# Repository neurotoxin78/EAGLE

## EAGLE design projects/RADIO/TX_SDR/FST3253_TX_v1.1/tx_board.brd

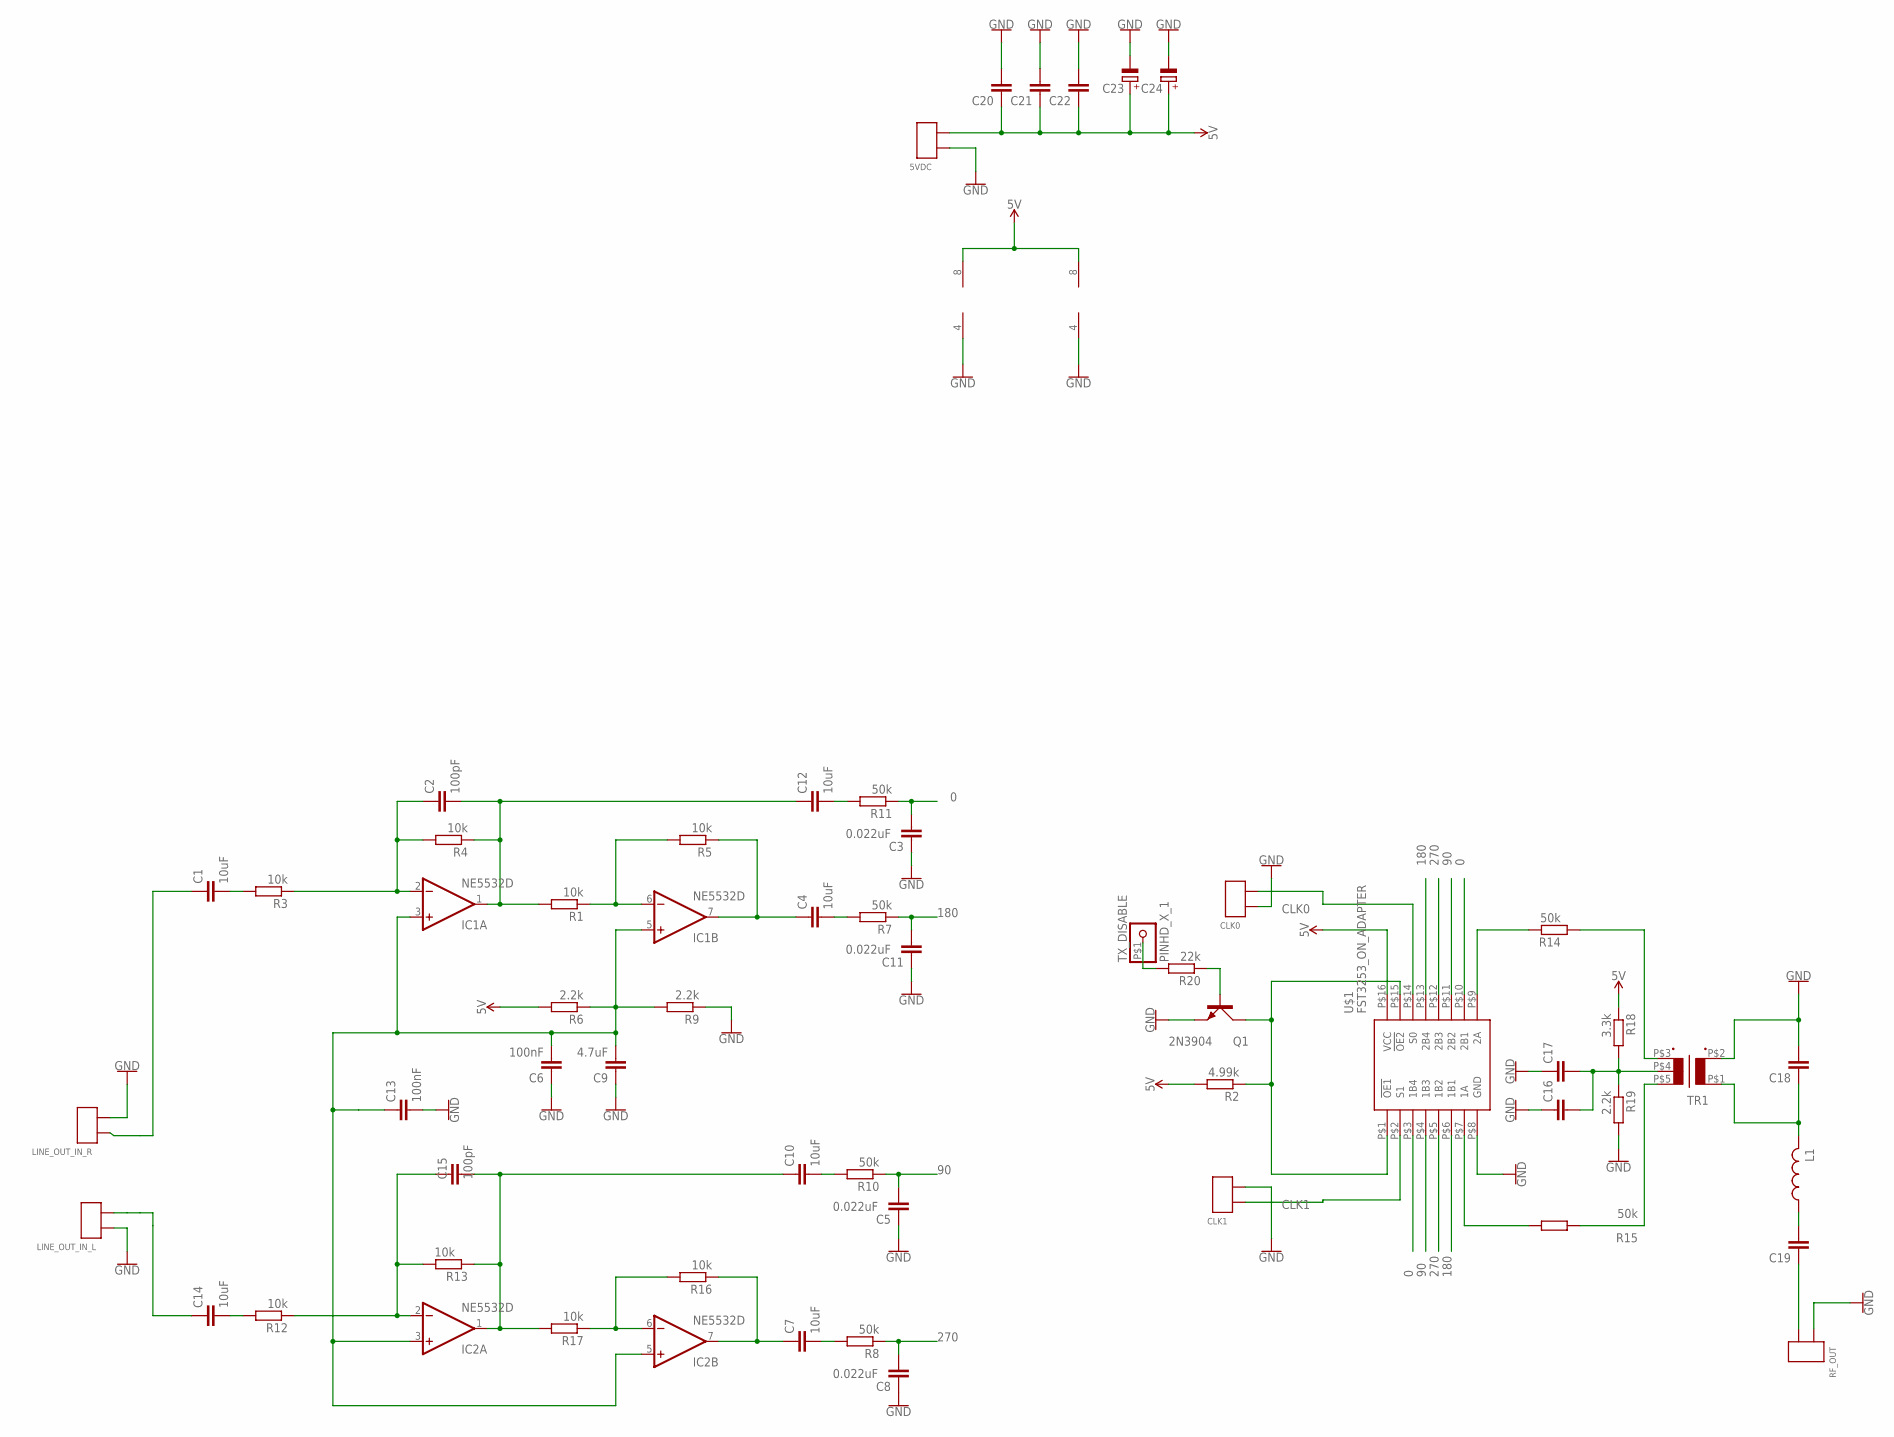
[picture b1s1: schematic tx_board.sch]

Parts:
5VDC: 2X_SMD_PTH_PIN; 2X_SMD_PTH
C1, C4, C7, C10, C12, C14: 10uF; C0805K
C2, C15: 100pF; C0805K
C3, C5, C8, C11: 0.022uF; C0805
C6, C13: 100nF; C0805
C9: 4.7uF; C0805
C16, C20, C21, C22: C_0805_SMD; C0805
C17, C18, C19: C_0805_PTH; C0805K
C23, C24: C_POL; E5-5
CLK0, CLK1: 2X_SMD_PTH_PIN; 2X_SMD_PTH
IC1, IC2: NE5532D; SO08
L1: L_0805_PTH; M0805
LINE_OUT_IN_L: 2X_SMD_PTH_PIN; 2X_SMD_PTH
LINE_OUT_IN_R: 2X_SMD_PTH_PIN; 2X_SMD_PTH
Q1: 2N3904; TO92D
R1, R3, R4, R12, R13, R16: 10k; R0805
R2: 4.99k; R0805W
R5, R17: 10k; R0805W
R6: 2.2k; 0204/7
R7, R8, R10, R11, R14, R15: 50k; R0805
R9, R19: 2.2k; R0805W
R18: 3.3k; R0805W
R20: 22k; R0805W
RF_OUT: 2X_SMD_PTH_PIN; 2X_SMD_PTH
TR1: 5PIN_TRANSFORMER
TX_DISABLE: PINHD_X_1; PINHD1
U$1: FST3253_ON_ADAPTER; SSOP16_ADAPTER

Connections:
0: C3.2, R11.1, R11.P$1 (1), U$1.P$3 (1B4), U$1.P$10 (2B1)
5V: 5VDC.P$2 (PIN1), 5VDC.T$2 (PIN1), C20.1, C21.1, C22.1, C23.+, C24.+, IC1.8 (V+), IC2.8 (V+), R2.2, R6.2, R18.1, U$1.P$16 (VCC)
90: C5.2, R10.1, R10.P$1 (1), U$1.P$4 (1B3), U$1.P$11 (2B2)
180: C11.2, R7.1, R7.P$1 (1), U$1.P$6 (1B1), U$1.P$13 (2B4)
270: C8.2, R8.1, R8.P$1 (1), U$1.P$5 (1B2), U$1.P$12 (2B3)
CLK0: CLK0.P$2 (PIN1), CLK0.T$2 (PIN1), U$1.P$14 (S0)
CLK1: CLK1.P$1 (PIN0), CLK1.T$1 (PIN0), U$1.P$2 (S1)
GND: 5VDC.P$1 (PIN0), 5VDC.T$1 (PIN0), C3.1, C5.1, C6.1, C8.1, C9.1, C11.1, C13.2, C16.1, C17.1, C17.P$1 (1), C18.2, C18.P$2 (2), C20.2, C21.2, C22.2, C23.-, C24.-, CLK0.P$1 (PIN0), CLK0.T$1 (PIN0), CLK1.P$2 (PIN1), CLK1.T$2 (PIN1), IC1.4 (V-), IC2.4 (V-), LINE_OUT_IN_L.P$1 (PIN0), LINE_OUT_IN_L.T$1 (PIN0), LINE_OUT_IN_R.P$2 (PIN1), LINE_OUT_IN_R.T$2 (PIN1), Q1.E, R9.1, R19.2, RF_OUT.P$1 (PIN0), RF_OUT.T$1 (PIN0), TR1.P$2 (2), U$1.P$8 (GND)
unnamed: Q1.C, R2.1, U$1.P$1 (!OE1), U$1.P$15 (!OE2)
unnamed: R15.2, R15.P$2 (2), U$1.P$7 (1A)
unnamed: R14.2, R14.P$2 (2), U$1.P$9 (2A)
unnamed: R14.1, R14.P$1 (1), TR1.P$3 (3)
unnamed: R15.1, R15.P$1 (1), TR1.P$5 (5)
unnamed: C16.2, C17.2, C17.P$2 (2), R18.2, R19.1, TR1.P$4 (4)
unnamed: C2.1, C2.P$1 (1), IC1.2 (-IN), R3.1, R3.P$1 (1), R4.2, R4.P$2 (2)
unnamed: C18.1, C18.P$1 (1), L1.2, L1.P$2 (2), TR1.P$1 (1)
unnamed: C19.2, C19.P$2 (2), L1.1, L1.P$1 (1)
unnamed: C2.2, C2.P$2 (2), C12.1, C12.P$1 (1), IC1.1 (OUT), R1.2, R1.P$2 (2), R4.1, R4.P$1 (1)
unnamed: IC1.6 (-IN), R1.1, R1.P$1 (1), R5.2
unnamed: C15.1, C15.P$1 (1), IC2.2 (-IN), R12.1, R12.P$1 (1), R13.2, R13.P$2 (2)
unnamed: C10.1, C10.P$1 (1), C15.2, C15.P$2 (2), IC2.1 (OUT), R13.1, R13.P$1 (1), R17.2
unnamed: IC2.6 (-IN), R16.2, R16.P$2 (2), R17.1
unnamed: C4.1, C4.P$1 (1), IC1.7 (OUT), R5.1
unnamed: C7.1, C7.P$1 (1), IC2.7 (OUT), R16.1, R16.P$1 (1)
unnamed: C4.2, C4.P$2 (2), R7.2, R7.P$2 (2)
unnamed: C19.1, C19.P$1 (1), RF_OUT.P$2 (PIN1), RF_OUT.T$2 (PIN1)
unnamed: C1.1, C1.P$1 (1), LINE_OUT_IN_R.P$1 (PIN0), LINE_OUT_IN_R.T$1 (PIN0)
unnamed: C14.1, C14.P$1 (1), LINE_OUT_IN_L.P$2 (PIN1), LINE_OUT_IN_L.T$2 (PIN1)
unnamed: Q1.B, R20.1
unnamed: C14.2, C14.P$2 (2), R12.2, R12.P$2 (2)
unnamed: C1.2, C1.P$2 (2), R3.2, R3.P$2 (2)
unnamed: R20.2, TX_DISABLE.P$1
unnamed: C12.2, C12.P$2 (2), R11.2, R11.P$2 (2)
unnamed: C10.2, C10.P$2 (2), R10.2, R10.P$2 (2)
unnamed: C7.2, C7.P$2 (2), R8.2, R8.P$2 (2)
unnamed: C6.2, C9.2, C13.1, IC1.3 (+IN), IC1.5 (+IN), IC2.3 (+IN), IC2.5 (+IN), R6.1, R9.2

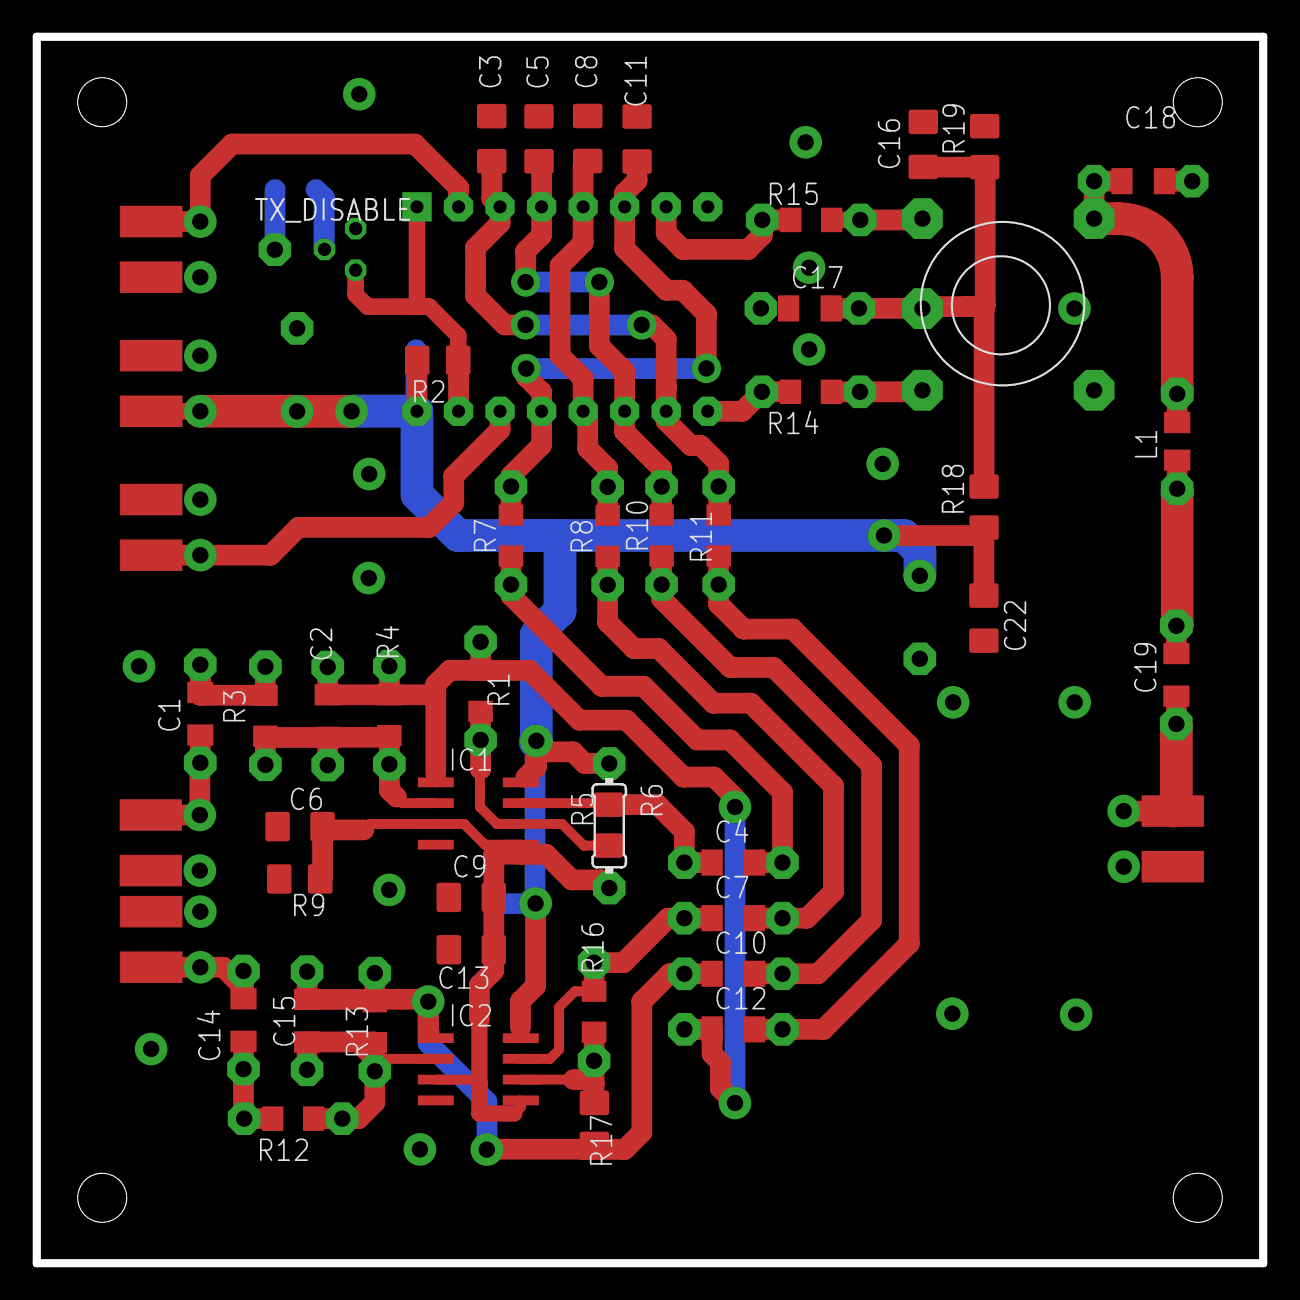
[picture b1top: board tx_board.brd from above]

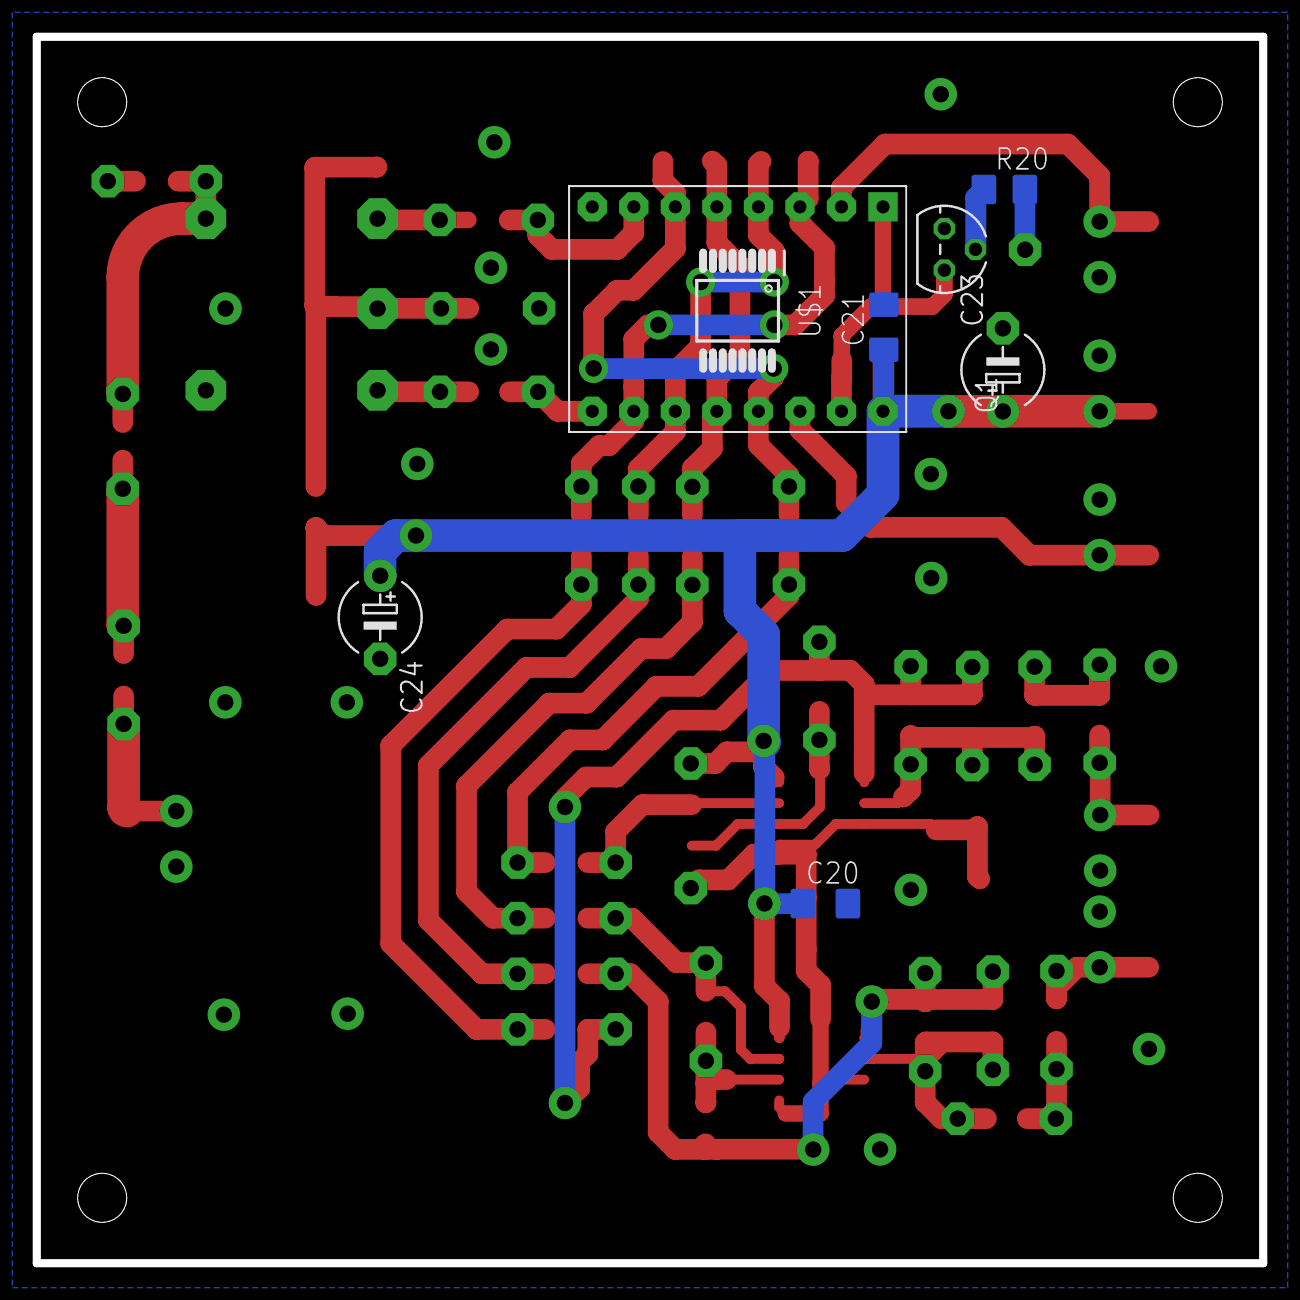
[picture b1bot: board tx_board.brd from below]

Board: 2 copper layers, 75.0 x 75.0 mm, 57 parts (7 on the bottom side), 36 nets.

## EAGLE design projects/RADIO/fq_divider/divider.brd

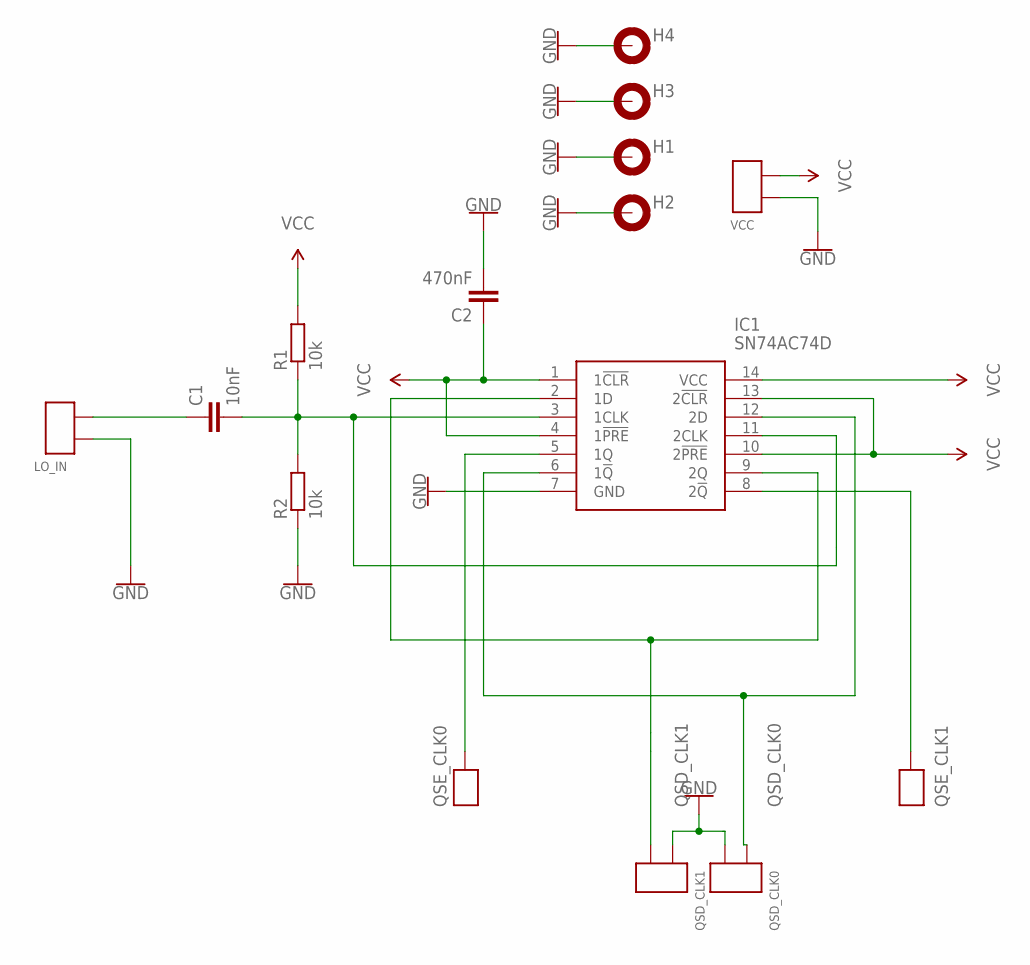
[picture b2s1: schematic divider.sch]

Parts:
C1: 10nF; C0805
C2: 470nF; C0805
H1, H2: MOUNT-PAD-ROUND3.0; 3,0-PAD
H3, H4: MOUNT-PAD-ROUND2.8; 2,8-PAD
IC1: SN74AC74D; SOIC127P600X175-14N
LO_IN: 2X_SMD_PTH_PIN; 2X_SMD_PTH
QSD_CLK0, QSD_CLK1: 2X_SMD_PTH_PIN; 2X_SMD_PTH
R1, R2: 10k; R0805W
TX_CLK0, TX_CLK1: SMD_PTH_PIN
VCC: 2X_SMD_PTH_PIN; 2X_SMD_PTH

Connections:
GND: C2.2, H1.B3,0, H2.B3,0, H3.B2,8, H4.B2,8, IC1.7 (GND), LO_IN.P$1 (PIN0), LO_IN.T$1 (PIN0), QSD_CLK0.P$2 (PIN1), QSD_CLK0.T$2 (PIN1), QSD_CLK1.P$1 (PIN0), QSD_CLK1.T$1 (PIN0), R2.1, VCC.P$1 (PIN0), VCC.T$1 (PIN0)
unnamed: C1.2, IC1.3 (1CLK), IC1.11 (2CLK), R1.1, R2.2
unnamed: C1.1, LO_IN.P$2 (PIN1), LO_IN.T$2 (PIN1)
QSD_CLK0: IC1.6 (1!Q), IC1.12 (2D), QSD_CLK0.P$1 (PIN0), QSD_CLK0.T$1 (PIN0)
QSD_CLK1: IC1.2 (1D), IC1.9 (2Q), QSD_CLK1.P$2 (PIN1), QSD_CLK1.T$2 (PIN1)
QSE_CLK0: IC1.5 (1Q), TX_CLK0.P$1, TX_CLK0.P$2
QSE_CLK1: IC1.8 (2!Q), TX_CLK1.P$1, TX_CLK1.P$2
VCC: C2.1, IC1.1 (1!CLR), IC1.4 (1!PRE), IC1.10 (2!PRE), IC1.13 (2!CLR), IC1.14 (VCC), R1.2, VCC.P$2 (PIN1), VCC.T$2 (PIN1)

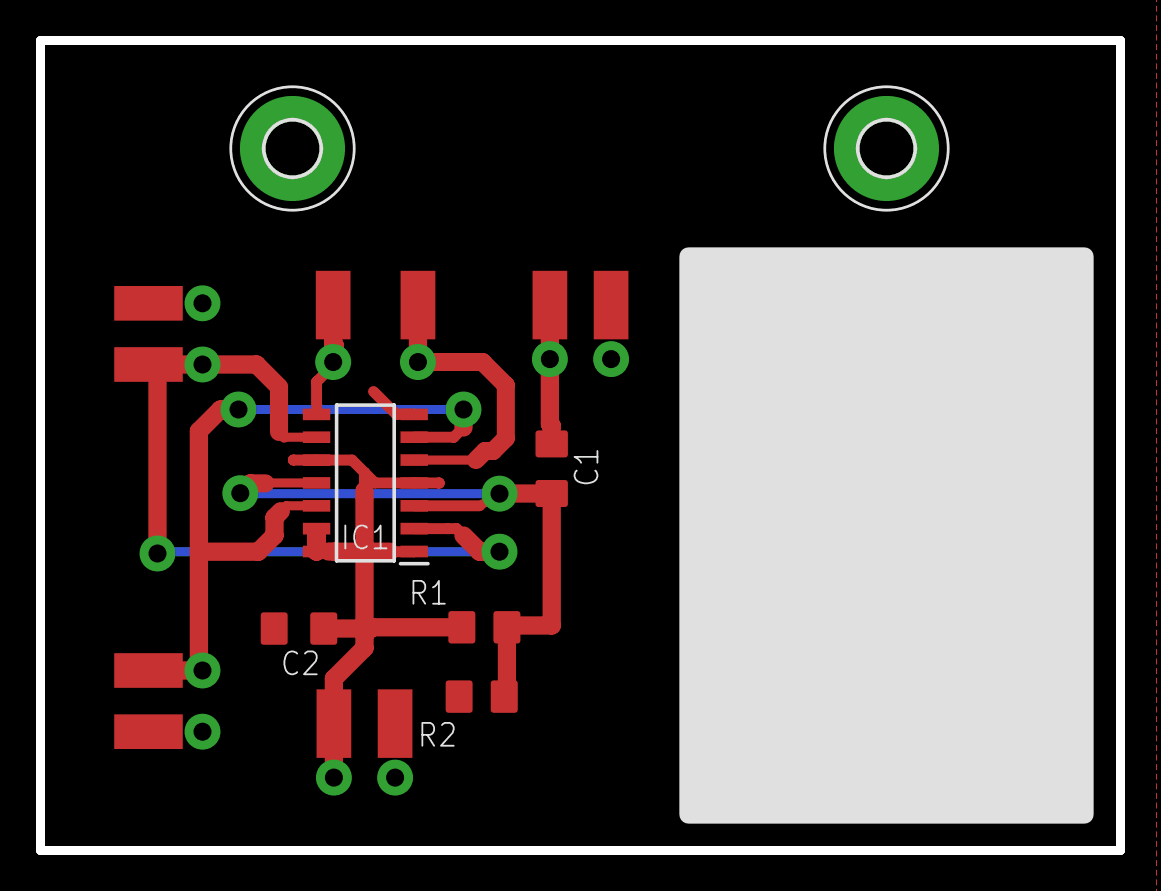
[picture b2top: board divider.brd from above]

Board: 2 copper layers, 60.0 x 45.0 mm, 15 parts (0 on the bottom side), 8 nets.

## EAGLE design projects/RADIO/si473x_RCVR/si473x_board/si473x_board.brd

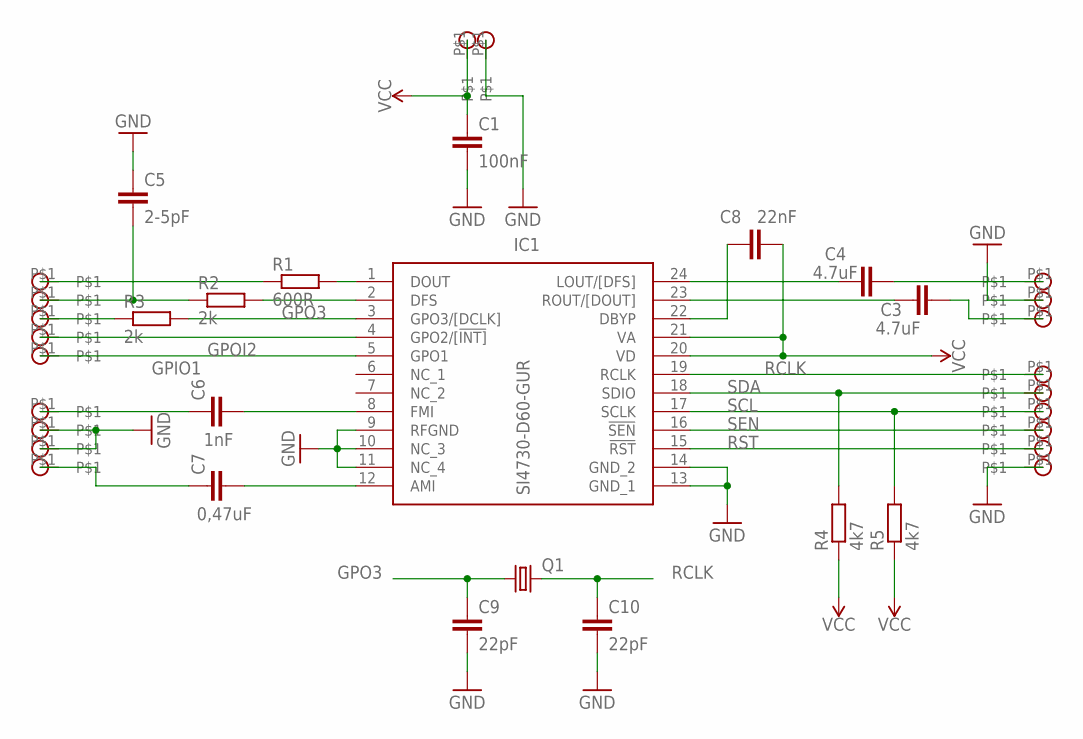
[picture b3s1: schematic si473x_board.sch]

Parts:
AMI: SMD_PIN
C1: 100nF; C0805
C3, C4: 4.7uF; C1210
C5: 2-5pF; C0805
C6: 1nF; C0805
C7: 0,47uF; C0805
C8: 22nF; C0805
C9, C10: 22pF; C0805
FMI: SMD_PIN
GND: SMD_PIN
IC1: SI4730-D60-GUR; SOP64P600X200-24N
Q1: KX-327-NHF; 3.2X1.5
R1: 600R; R0805
R2, R3: 2k; R0805
R4, R5: 4k7; 0204/7
U$1, U$2, U$3, U$4, U$5, U$8, U$10, U$11, U$12, U$13, U$14, U$15, U$16, U$17, U$18, U$19, U$20: SMD_PIN

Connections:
GND: C1.2, C5.1, C9.2, C10.2, GND.P$1, IC1.9 (RFGND), IC1.10 (NC_3), IC1.11 (NC_4), IC1.13 (GND_1), IC1.14 (GND_2), U$8.P$1, U$11.P$1, U$13.P$1, U$20.P$1
GPIO1: IC1.5 (GPO1), U$5.P$1
GPO3: C9.1, IC1.3 (GPO3/[DCLK]), Q1.1, R3.2
GPOI2: IC1.4 (GPO2/[!INT]), U$4.P$1
unnamed: IC1.1 (DOUT), R1.2
unnamed: IC1.2 (DFS), R2.2
unnamed: R1.1, U$1.P$1
unnamed: C5.2, R2.1, U$2.P$1
unnamed: R3.1, U$3.P$1
unnamed: C3.1, IC1.23 (ROUT/[DOUT])
unnamed: C3.2, U$14.P$1
unnamed: C4.1, IC1.24 (LOUT/[DFS])
unnamed: C4.2, U$12.P$1
unnamed: C8.2, IC1.22 (DBYP)
unnamed: C6.1, FMI.P$1
unnamed: C6.2, IC1.8 (FMI)
unnamed: C7.2, IC1.12 (AMI)
unnamed: AMI.P$1, C7.1
RCLK: C10.1, IC1.19 (RCLK), Q1.2, U$15.P$1
RST: IC1.15 (!RST), U$19.P$1
SCL: IC1.17 (SCLK), R5.2, U$17.P$1
SDA: IC1.18 (SDIO), R4.2, U$16.P$1
SEN: IC1.16 (!SEN), U$18.P$1
VCC: C1.1, C8.1, IC1.20 (VD), IC1.21 (VA), R4.1, R5.1, U$10.P$1

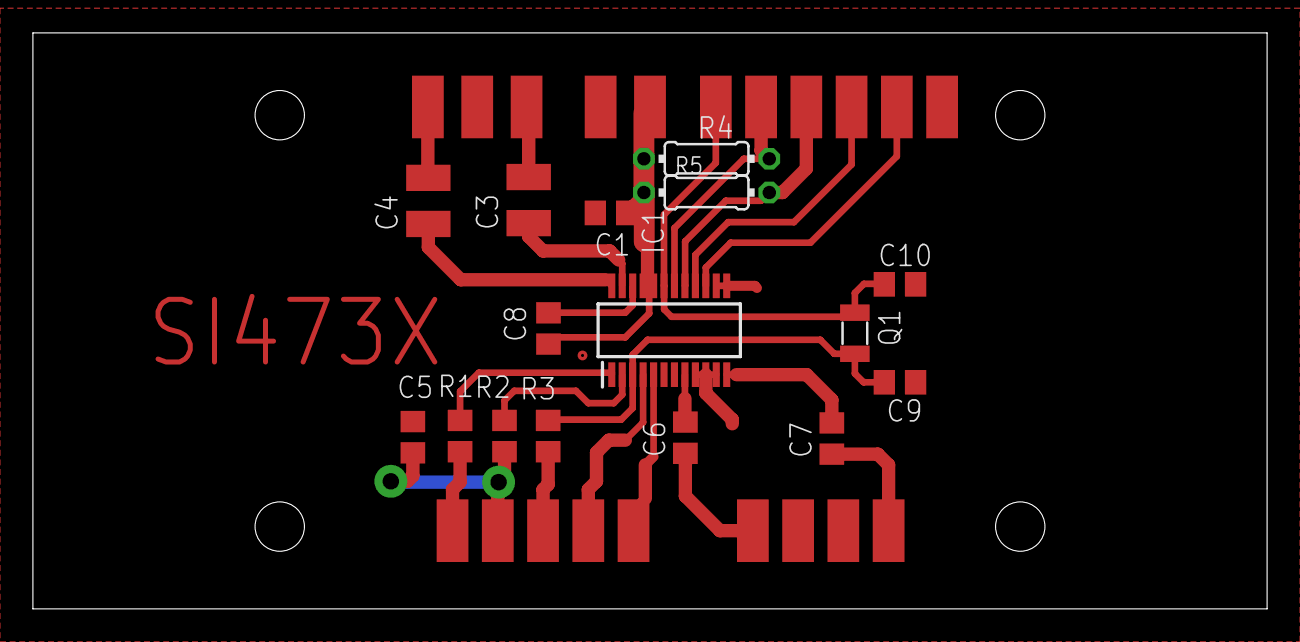
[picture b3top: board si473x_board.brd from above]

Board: 2 copper layers, 75.0 x 35.0 mm, 36 parts (0 on the bottom side), 24 nets.

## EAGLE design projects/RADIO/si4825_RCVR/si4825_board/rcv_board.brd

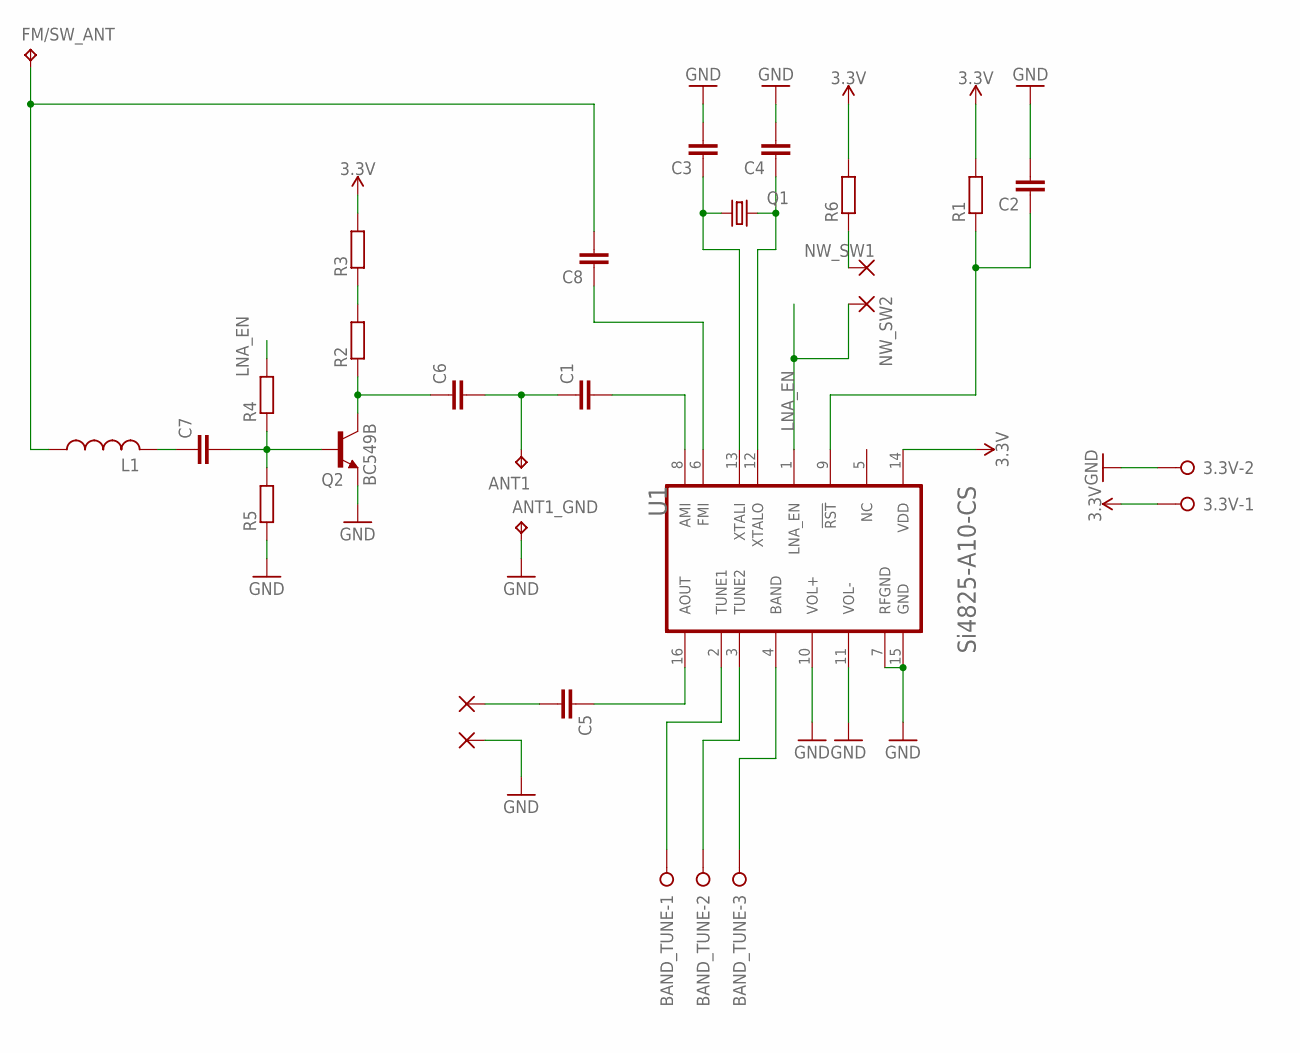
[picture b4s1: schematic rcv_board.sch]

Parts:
3.3V: W237-02P; W237-132
ANT1, ANT1_GND: TPPAD1-20Y; P1-20Y
BAND_TUNE: W237-03P; W237-133
C1, C2, C3, C4, C6, C7, C8: C-EUC0805; C0805
C5: C-EU050-035X075; C050-035X075
FM/SW_ANT: TPPAD1-17; P1-17
L1: L-US0204V; 0204V
OGND: NW_SW1; 2,54/1,0
OUT: NW_SW1; 2,54/1,0
PAD1: NW_SW1; 2,54/1,0
PAD2: NW_SW2; 2,54/1,0
Q1: KX-327-NHF; 3.2X1.5
Q2: BC549B; TO92-EBC
R1, R2, R3, R4, R5, R6: R-EU_R0805; R0805
U1: SILICON_LABS_SI4825-A10-CSSILICON_LABS_SI4825-A10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; SILICON_LABS_SI4825-A10-CS_2

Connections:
3.3V: 3.3V.1, R1.2, R3.2, R6.2, U1.14 (VDD)
GND: 3.3V.2, ANT1_GND.TP, C2.2, C3.2, C4.2, OGND.1, Q2.E, R5.1, U1.7 (RFGND), U1.10 (VOL+), U1.11 (VOL-), U1.15 (GND)
LNA_EN: PAD2.1, R4.2, U1.1 (LNA_EN)
unnamed: C1.2, U1.8 (AMI)
unnamed: C2.1, R1.1, U1.9 (!RST!)
unnamed: C4.1, Q1.2, U1.12 (XTALO)
unnamed: C3.1, Q1.1, U1.13 (XTALI)
unnamed: C5.1, U1.16 (AOUT)
unnamed: C6.1, Q2.C, R2.1
unnamed: ANT1.TP, C1.1, C6.2
unnamed: R2.2, R3.1
unnamed: C7.2, Q2.B, R4.1, R5.2
unnamed: C8.1, U1.6 (FMI)
unnamed: C7.1, L1.2
unnamed: C8.2, FM/SW_ANT.TP, L1.1
unnamed: PAD1.1, R6.1
unnamed: BAND_TUNE.3, U1.4 (BAND)
unnamed: BAND_TUNE.2, U1.3 (TUNE2)
unnamed: BAND_TUNE.1, U1.2 (TUNE1)
unnamed: C5.2, OUT.1

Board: 2 copper layers, 27 parts (2 on the bottom side), 20 nets, no tracks yet.

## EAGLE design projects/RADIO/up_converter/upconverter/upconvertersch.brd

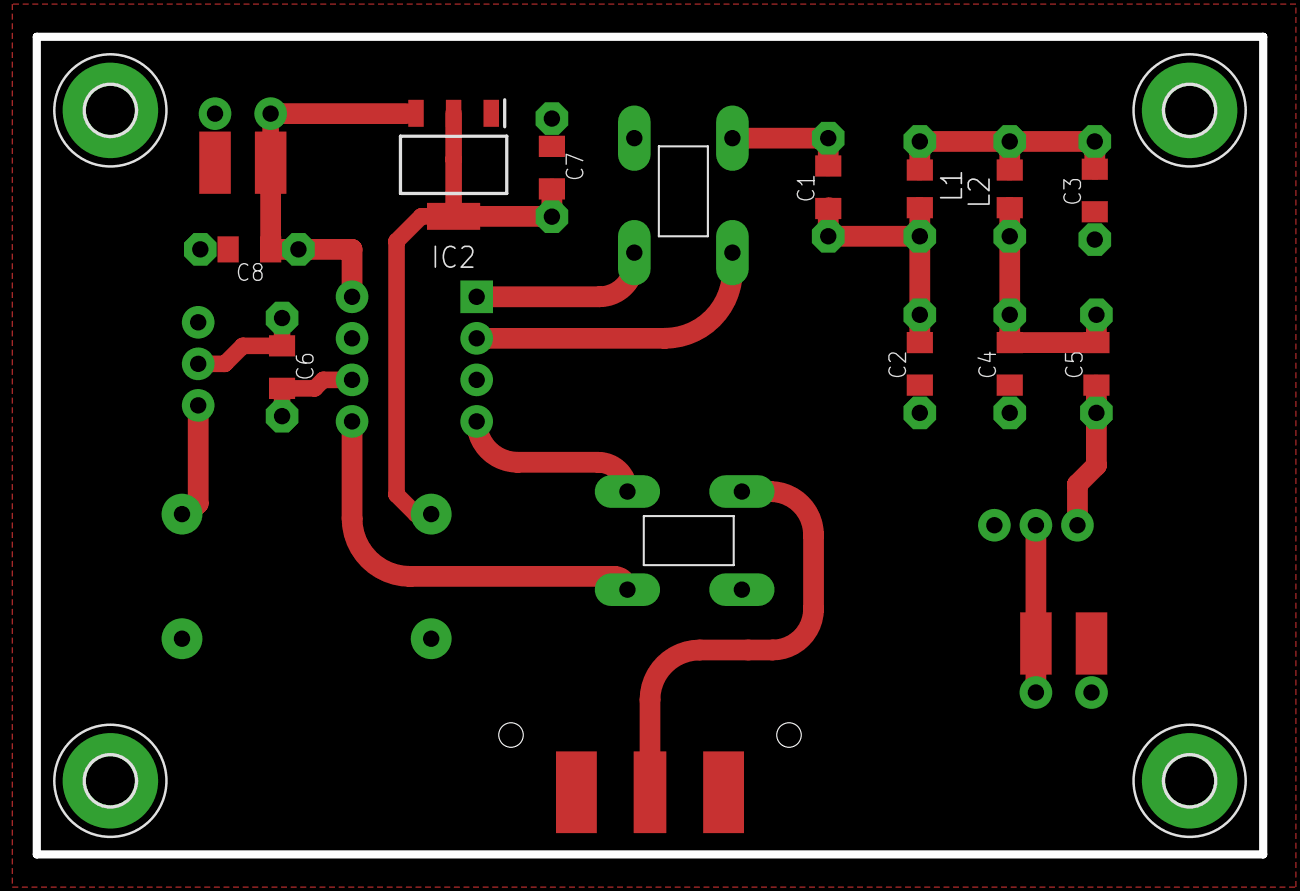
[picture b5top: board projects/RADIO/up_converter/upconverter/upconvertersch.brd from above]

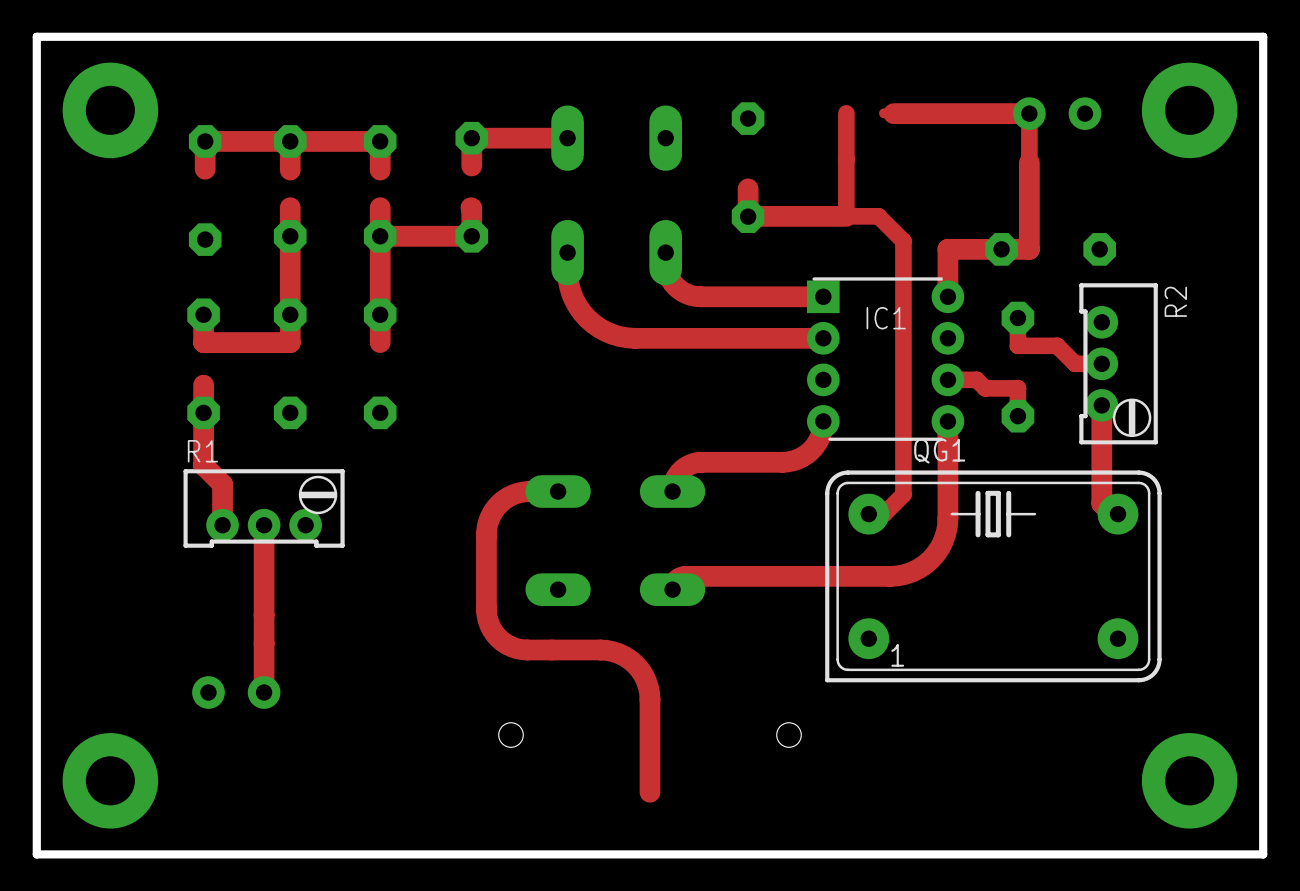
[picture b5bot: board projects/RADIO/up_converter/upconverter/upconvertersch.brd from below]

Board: 2 copper layers, 75.0 x 50.0 mm, 24 parts (4 on the bottom side), 17 nets.

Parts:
5V: 2X_SMD_PTH_PIN; 2X_SMD_PTH
C1, C5, C6, C7, C8: 100nF; C0805K
C2, C4: 100pF; C0805K
C3: 200pF; C0805K
H1, H2, H3, H4: MOUNT-PAD-ROUND3.0; 3,0-PAD
IC1: SA612AN_01,112; DIP762W53P254L950H420Q8N
IC2: LD1117STR; SOT230P700X180-4N
L1, L2: M0805
QG1: DIL14S
R1, R2: RTRIM64W
RF_IN: 2X_SMD_PTH_PIN; 2X_SMD_PTH
T1, T2: TRANSFORMER
U$1: RTL_SDR_CONN; RTL_SDR_OUT

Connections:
3.3V: C7.2, C7.P$2, IC2.2, IC2.4, QG1.14
GND: 5V.P$1, 5V.T$1, C2.1, C2.P$1, C3.1, C3.P$1, C4.1, C4.P$1, C7.1, C7.P$1, C8.2, C8.P$2, H1.B3,0, H2.B3,0, H3.B3,0, H4.B3,0, IC1.3, IC2.1, QG1.7, R1.3, R2.1, RF_IN.P$1, RF_IN.T$1, T1.P$2, T2.P$1, U$1.P$2, U$1.P$3
unnamed: IC1.1, T1.P$4
unnamed: IC1.2, T1.P$3
unnamed: IC1.4, T2.P$4
unnamed: IC1.5, T2.P$3
unnamed: C1.2, C1.P$2, T1.P$1
unnamed: C1.1, C1.P$1, C2.2, C2.P$2, L1.2, L1.P$2
unnamed: C3.2, C3.P$2, L1.1, L1.P$1, L2.2, L2.P$2
unnamed: C4.2, C4.P$2, C5.2, C5.P$2, L2.1, L2.P$1
unnamed: C5.1, C5.P$1, R1.1
unnamed: R1.2, RF_IN.P$2, RF_IN.T$2
unnamed: QG1.8, R2.3
unnamed: T2.P$2, U$1.P$1
unnamed: C6.1, C6.P$1, R2.2
unnamed: C6.2, C6.P$2, IC1.6
VCC: 5V.P$2, 5V.T$2, C8.1, C8.P$1, IC1.8, IC2.3

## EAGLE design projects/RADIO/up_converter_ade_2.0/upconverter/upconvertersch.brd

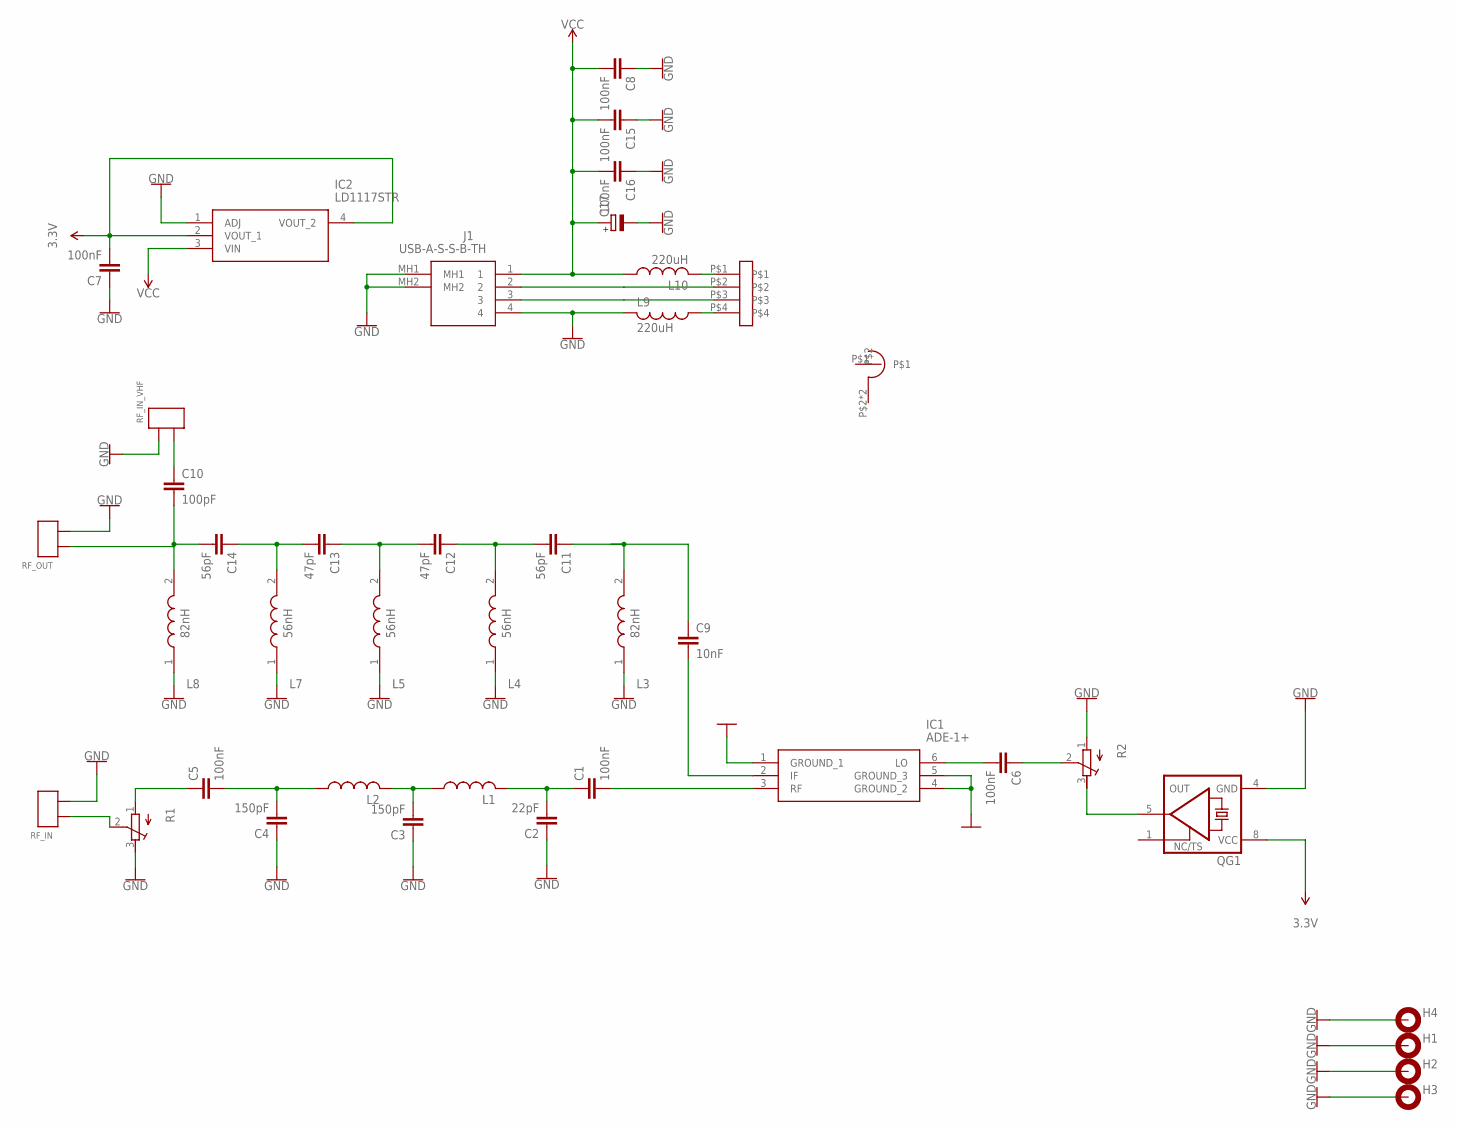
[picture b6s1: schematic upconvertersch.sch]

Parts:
C1, C5, C6, C7, C8, C15, C16: 100nF; C0805K
C2: 22pF; C0805K
C3, C4: 150pF; C0805K
C9: 10nF; C0805K
C10: 100pF; C0805K
C11, C14: 56pF; C0805K
C12, C13: 47pF; C0805K
C17: CPOL-EUE3.5-10; E3,5-10
H1, H2, H3, H4: MOUNT-PAD-ROUND3.0; 3,0-PAD
IC1: ADE-1+; ADE1
IC2: LD1117STR; SOT230P700X180-4N
J1: USB-A-S-S-B-TH; USBASSBTH
JH1: 4X_PIN_HEADER
L1, L2: L_0805_PTH; M0805
L3, L8: 82nH; 16411A06L
L4, L5, L7: 56nH; 16411A06L
L9, L10: 220uH; M0805
QG1: XO-8; DIL08S
R1, R2: R-TRIMM64W; RTRIM64W
RF_IN: 2X_SMD_PTH_PIN; 2X_SMD_PTH
RF_IN_VHF: 2X_SMD_PTH_PIN; 2X_SMD_PTH
RF_OUT: 2X_SMD_PTH_PIN; 2X_SMD_PTH
U$1: RTL_SDR_CONN; RTL_SDR_OUT

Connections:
3.3V: C7.2, C7.P$2 (2), IC2.2 (VOUT_1), IC2.4 (VOUT_2), QG1.8 (VCC)
GND: C2.1, C2.P$1 (1), C3.1, C3.P$1 (1), C4.1, C4.P$1 (1), C7.1, C7.P$1 (1), C8.1, C8.P$1 (1), C15.1, C15.P$1 (1), C16.1, C16.P$1 (1), C17.-, H1.B3,0, H2.B3,0, H3.B3,0, H4.B3,0, IC1.1 (GROUND_1), IC1.4 (GROUND_2), IC1.5 (GROUND_3), IC2.1 (ADJ), J1.4, J1.MH1, J1.MH2, L3.1, L4.1, L5.1, L7.1, L8.1, L9.2, L9.P$2 (2), QG1.4 (GND), R1.3 (E), R2.1 (A), RF_IN.P$2 (PIN1), RF_IN.T$2 (PIN1), RF_IN_VHF.P$1 (PIN0), RF_IN_VHF.T$1 (PIN0), RF_OUT.P$2 (PIN1), RF_OUT.T$2 (PIN1)
unnamed: C1.2, C1.P$2 (2), IC1.3 (RF)
unnamed: C9.2, C9.P$2 (2), IC1.2 (IF)
unnamed: C6.2, C6.P$2 (2), IC1.6 (LO)
unnamed: J1.2, JH1.P$2
unnamed: J1.3, JH1.P$3
unnamed: C1.1, C1.P$1 (1), C2.2, C2.P$2 (2), L1.2, L1.P$2 (2)
unnamed: C3.2, C3.P$2 (2), L1.1, L1.P$1 (1), L2.2, L2.P$2 (2)
unnamed: C4.2, C4.P$2 (2), C5.2, C5.P$2 (2), L2.1, L2.P$1 (1)
unnamed: C5.1, C5.P$1 (1), R1.1 (A)
unnamed: R1.2 (S), RF_IN.P$1 (PIN0), RF_IN.T$1 (PIN0)
unnamed: QG1.5 (OUT), R2.3 (E)
unnamed: C10.1, C10.P$1 (1), RF_IN_VHF.P$2 (PIN1), RF_IN_VHF.T$2 (PIN1)
unnamed: C6.1, C6.P$1 (1), R2.2 (S)
unnamed: C9.1, C9.P$1 (1), C11.1, C11.P$1 (1), L3.2
unnamed: C11.2, C11.P$2 (2), C12.1, C12.P$1 (1), L4.2
unnamed: C12.2, C12.P$2 (2), C13.1, C13.P$1 (1), L5.2
unnamed: C10.2, C10.P$2 (2), C14.2, C14.P$2 (2), L8.2, RF_OUT.P$1 (PIN0), RF_OUT.T$1 (PIN0)
unnamed: C13.2, C13.P$2 (2), C14.1, C14.P$1 (1), L7.2
unnamed: JH1.P$4, L9.1, L9.P$1 (1)
unnamed: JH1.P$1, L10.2, L10.P$2 (2)
VCC: C8.2, C8.P$2 (2), C15.2, C15.P$2 (2), C16.2, C16.P$2 (2), C17.+, IC2.3 (VIN), J1.1, L10.1, L10.P$1 (1)

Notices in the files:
parts and their libraries:
SparkFun-PowerSymbols: Licensing: Creative Commons ShareAlike 4.0 International - https://creativecommons.org/licenses/by-sa/4.0
crystal-geyer_V1_0: Copyright: Geyer-Electronic
